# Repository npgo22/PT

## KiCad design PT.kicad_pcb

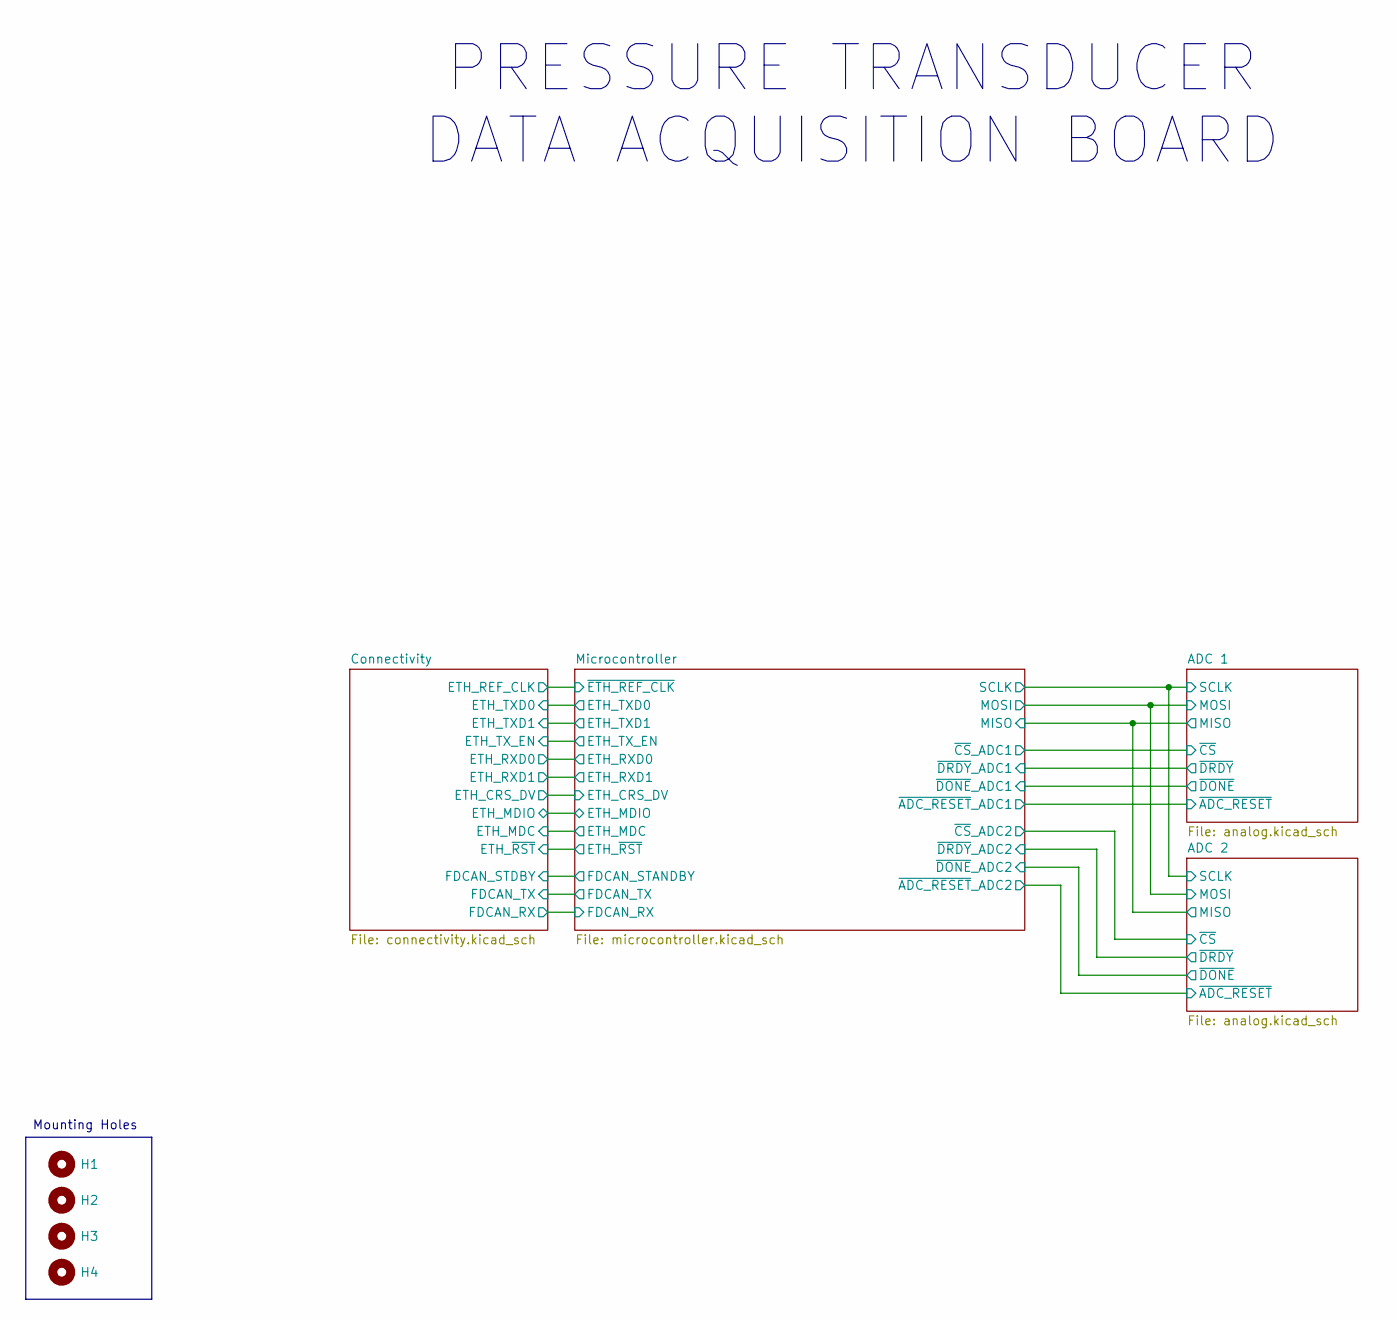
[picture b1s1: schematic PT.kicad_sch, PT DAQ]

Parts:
H1, H2, H3, H4: MountingHole; MountingHole_3.2mm_M3

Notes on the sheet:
PRESSURE TRANSDUCER DATA ACQUISITION BOARD
Mounting Holes

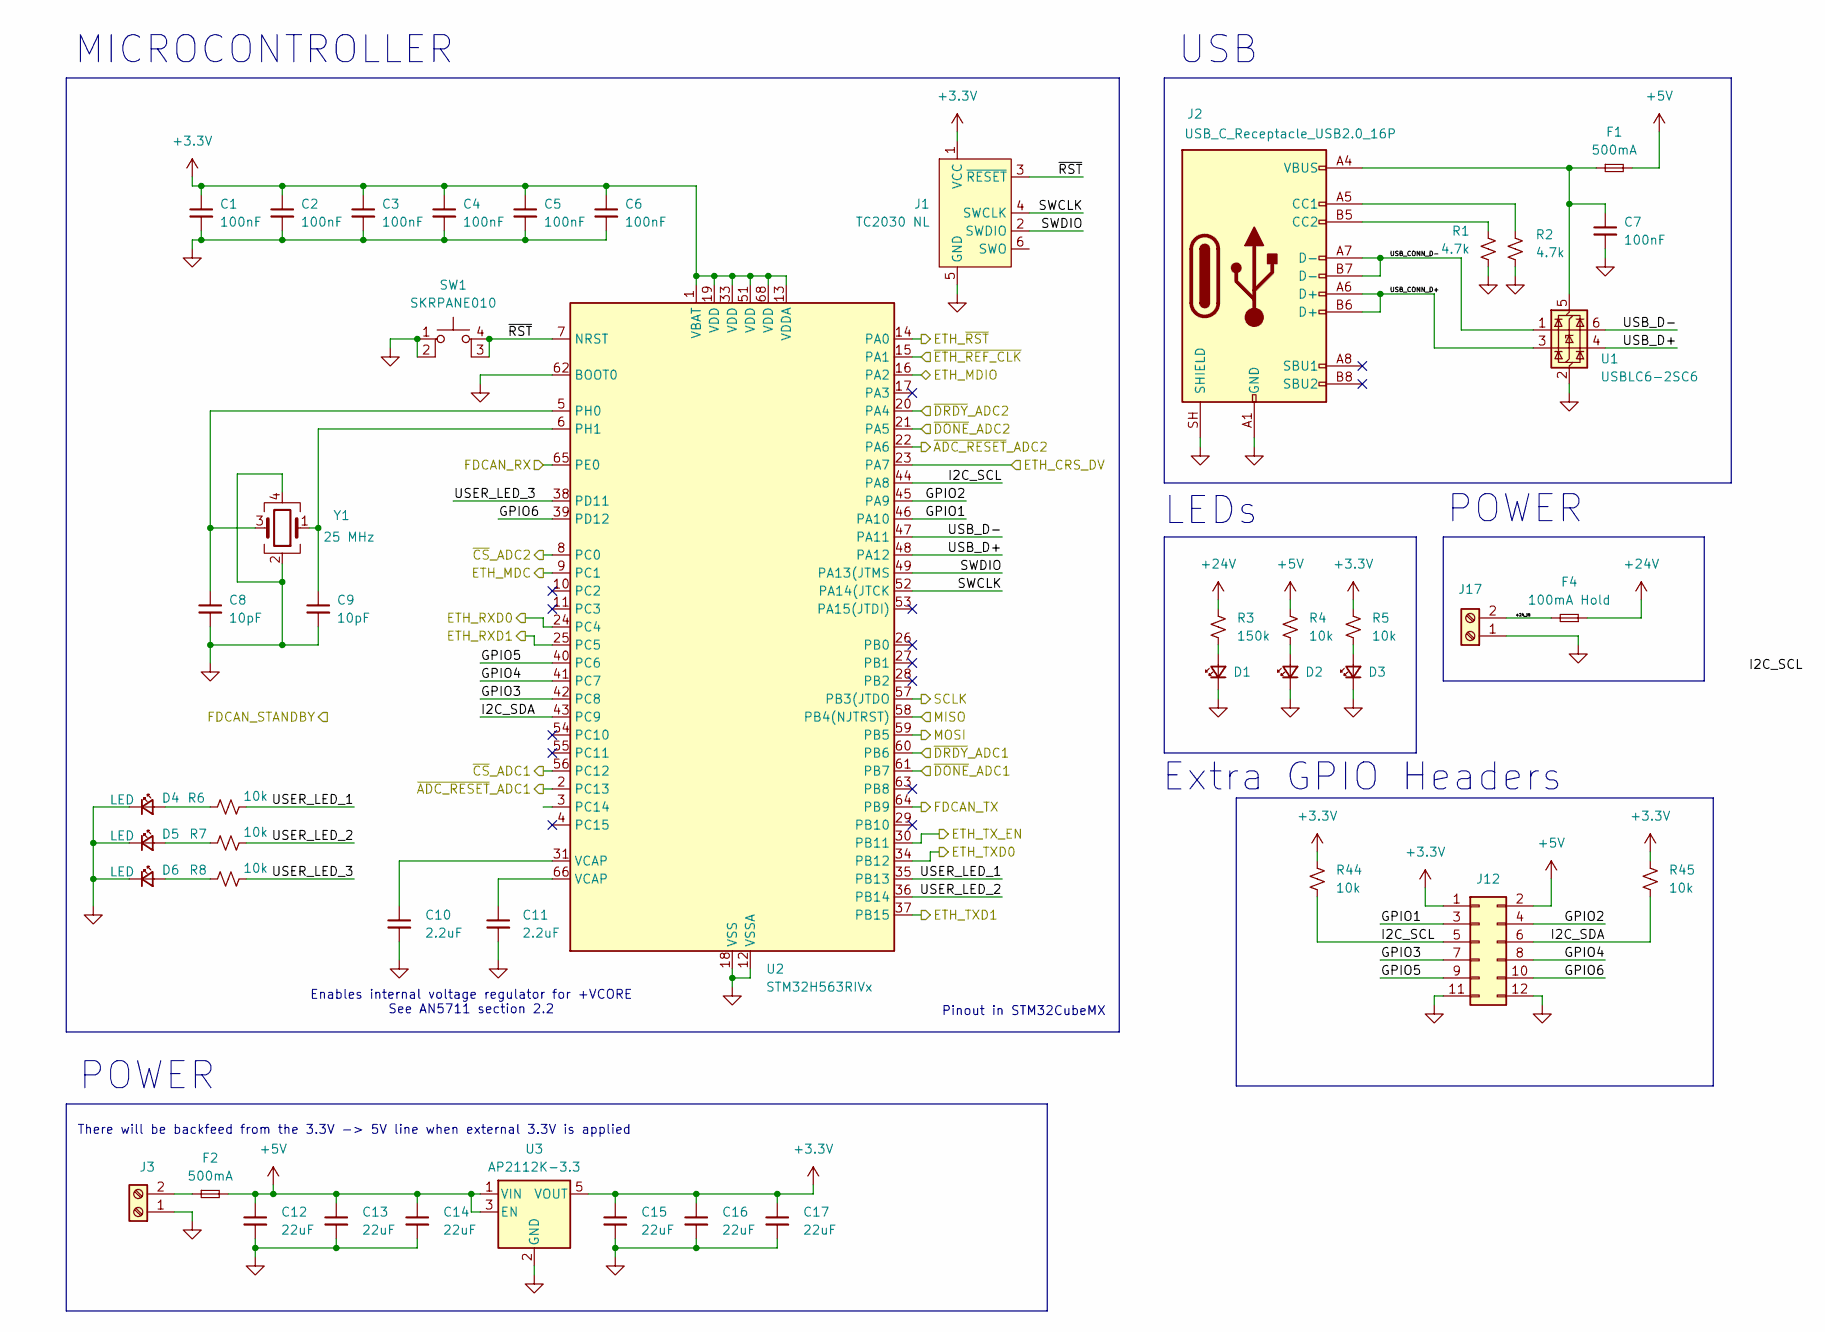
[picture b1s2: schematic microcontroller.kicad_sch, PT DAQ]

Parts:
C1, C2, C3, C4, C5, C6: 100nF; C_0603; LCSC C32949
C7: 100nF; C_0603
C8, C9: 10pF; C_0603; LCSC C32949
C10, C11: 2.2uF; C_0603; LCSC C170151
C12, C13, C14, C15, C16, C17: 22uF; C_0805; LCSC C602037
D1, D2, D3: LED; LED_0603
D4, D5, D6: LED; LED_0603; LCSC C965793
F1, F2: 500mA; Fuse_0805_2012Metric
F4: 100mA Hold; Fuse_0805_2012Metric
J1: TC2030 NL; Tag-Connect_TC2030-IDC-NL_2x03_P1.27mm_Vertical
J2: USB_C_Receptacle_USB2.0_16P; USB_C_Receptacle_HRO_TYPE-C-31-M-12
J3: Screw_Terminal_01x02; TerminalBlock_Phoenix_MPT-0,5-2-2.54_1x02_P2.54mm_Horizontal; LCSC C3029316
J12: Conn_02x06_Top_Bottom; IDC-Header_2x06_P2.54mm_Vertical
J17: Screw_Terminal_01x02; TerminalBlock_Phoenix_MPT-0,5-2-2.54_1x02_P2.54mm_Horizontal
R1, R2: 4.7k; R_0603
R3: 150k; R_0603
R4, R5, R44, R45: 10k; R_0603
R6, R7, R8: 10k; R_0603; LCSC C105875
SW1: SKRPANE010
U1: USBLC6-2SC6; SOT-23-6
U2: STM32H563RIVx; QFN-68-1EP_8x8mm_P0.4mm_EP6.4x6.4mm
U3: AP2112K-3.3; SOT-23-5
Y1: 25 MHz; 3225-4P-L; LCSC C2901668

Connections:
+3.3V: C1.1, C2.1, C3.1, C4.1, C5.1, C6.1, C15.1, C16.1, C17.1, J1.1 (VCC), J12.1, R5.1, R44.1, R45.1, U2.1 (VBAT), U2.13 (VDDA), U2.19 (VDD), U2.33 (VDD), U2.51 (VDD), U2.68 (VDD), U3.5 (VOUT); also elsewhere on the board
+5V: C12.1, C13.1, C14.1, F1.2, F2.2, J12.2, R4.1, U3.1 (VIN), U3.3 (EN); also elsewhere on the board
+24V: F4.1, R3.1; also elsewhere on the board
/ADC 1/MISO: U2.58 (PB4(NJTRST)); also elsewhere on the board
/ADC 1/MOSI: U2.59 (PB5); also elsewhere on the board
/ADC 1/SCLK: U2.57 (PB3(JTDO); also elsewhere on the board
/ADC 1/~ADC_RESET: U2.2 (PC13); also elsewhere on the board
/ADC 1/~CS: U2.56 (PC12); also elsewhere on the board
/ADC 1/~DONE: U2.61 (PB7); also elsewhere on the board
/ADC 1/~DRDY: U2.60 (PB6); also elsewhere on the board
/ADC 2/~ADC_RESET: U2.22 (PA6); also elsewhere on the board
/ADC 2/~CS: U2.8 (PC0); also elsewhere on the board
/ADC 2/~DONE: U2.21 (PA5); also elsewhere on the board
/ADC 2/~DRDY: U2.20 (PA4); also elsewhere on the board
/Connectivity/ETH_CRS_DV: U2.23 (PA7); also elsewhere on the board
/Connectivity/ETH_MDC: U2.9 (PC1); also elsewhere on the board
/Connectivity/ETH_MDIO: U2.16 (PA2); also elsewhere on the board
/Connectivity/ETH_REF_CLK: U2.15 (PA1); also elsewhere on the board
/Connectivity/ETH_RXD0: U2.24 (PC4); also elsewhere on the board
/Connectivity/ETH_RXD1: U2.25 (PC5); also elsewhere on the board
/Connectivity/ETH_TXD0: U2.34 (PB12); also elsewhere on the board
/Connectivity/ETH_TXD1: U2.37 (PB15); also elsewhere on the board
/Connectivity/ETH_TX_EN: U2.30 (PB11); also elsewhere on the board
/Connectivity/ETH_~RST: U2.14 (PA0); also elsewhere on the board
/Connectivity/FDCAN_RX: U2.65 (PE0); also elsewhere on the board
/Connectivity/FDCAN_TX: U2.64 (PB9); also elsewhere on the board
/Microcontroller/+24_IN: F4.2, J17.2
/Microcontroller/GPIO1: J12.3, U2.46 (PA10)
/Microcontroller/GPIO2: J12.4, U2.45 (PA9)
/Microcontroller/GPIO3: J12.7, U2.42 (PC8)
/Microcontroller/GPIO4: J12.8, U2.41 (PC7)
/Microcontroller/GPIO5: J12.9, U2.40 (PC6)
/Microcontroller/GPIO6: J12.10, U2.39 (PD12)
/Microcontroller/I2C_SCL: J12.5, R44.2, U2.44 (PA8)
/Microcontroller/I2C_SDA: J12.6, R45.2, U2.43 (PC9)
/Microcontroller/SWCLK: J1.4 (SWCLK), U2.52 (PA14(JTCK)
/Microcontroller/SWDIO: J1.2 (SWDIO), U2.49 (PA13(JTMS)
/Microcontroller/USB_CONN_D+: J2.A6 (D+), J2.B6 (D+), U1.3 (I/O2)
/Microcontroller/USB_CONN_D-: J2.A7 (D-), J2.B7 (D-), U1.1 (I/O1)
/Microcontroller/USB_D+: U1.4 (I/O2), U2.48 (PA12)
/Microcontroller/USB_D-: U1.6 (I/O1), U2.47 (PA11)
/Microcontroller/USER_LED_1: R6.2, U2.35 (PB13)
/Microcontroller/USER_LED_2: R7.2, U2.36 (PB14)
/Microcontroller/USER_LED_3: R8.2, U2.38 (PD11)
/Microcontroller/~RST: J1.3 (~RESET), SW1.3 (K), SW1.4 (A), U2.7 (NRST)
GND: C1.2, C2.2, C3.2, C4.2, C5.2, C6.2, C7.2, C8.2, C9.2, C10.2, C11.2, C12.2, C13.2, C14.2, C15.2, C16.2, C17.2, D1.1 (K), D2.1 (K), D3.1 (K), D4.1 (K), D5.1 (K), D6.1 (K), J1.5 (GND), J2.A1 (GND), J2.A12 (GND), J2.B1 (GND), J2.B12 (GND), J2.SH (SHIELD), J3.1, J12.11, J12.12, J17.1, R1.1, R2.2, SW1.1, SW1.2, U1.2 (GND), U2.12 (VSSA), U2.18 (VSS), U2.32 (VSS), U2.50 (VSS), U2.62 (BOOT0), U2.67 (VSS), U2.69 (VSS), U3.2 (GND), Y1.2, Y1.4; also elsewhere on the board
unnamed: C10.1, U2.31 (VCAP)
unnamed: C11.1, U2.66 (VCAP)
unnamed: D1.2 (A), R3.2
unnamed: D2.2 (A), R4.2
unnamed: D3.2 (A), R5.2
unnamed: D4.2 (A), R6.1
unnamed: D5.2 (A), R7.1
unnamed: D6.2 (A), R8.1
unnamed: J2.A5 (CC1), R2.1
unnamed: J2.B5 (CC2), R1.2
unnamed: F2.1, J3.2
unnamed: C7.1, F1.1, J2.A4 (VBUS), J2.A9 (VBUS), J2.B4 (VBUS), J2.B9 (VBUS), U1.5 (VBUS)
unnamed: C8.1, U2.5 (PH0), Y1.3
unnamed: C9.1, U2.6 (PH1), Y1.1

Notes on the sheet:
Enables internal voltage regulator for +VCORE See AN5711 section 2.2
MICROCONTROLLER
There will be backfeed from the 3.3V -> 5V line when external 3.3V is applied
Extra GPIO Headers
USB
POWER
Pinout in STM32CubeMX
LEDs

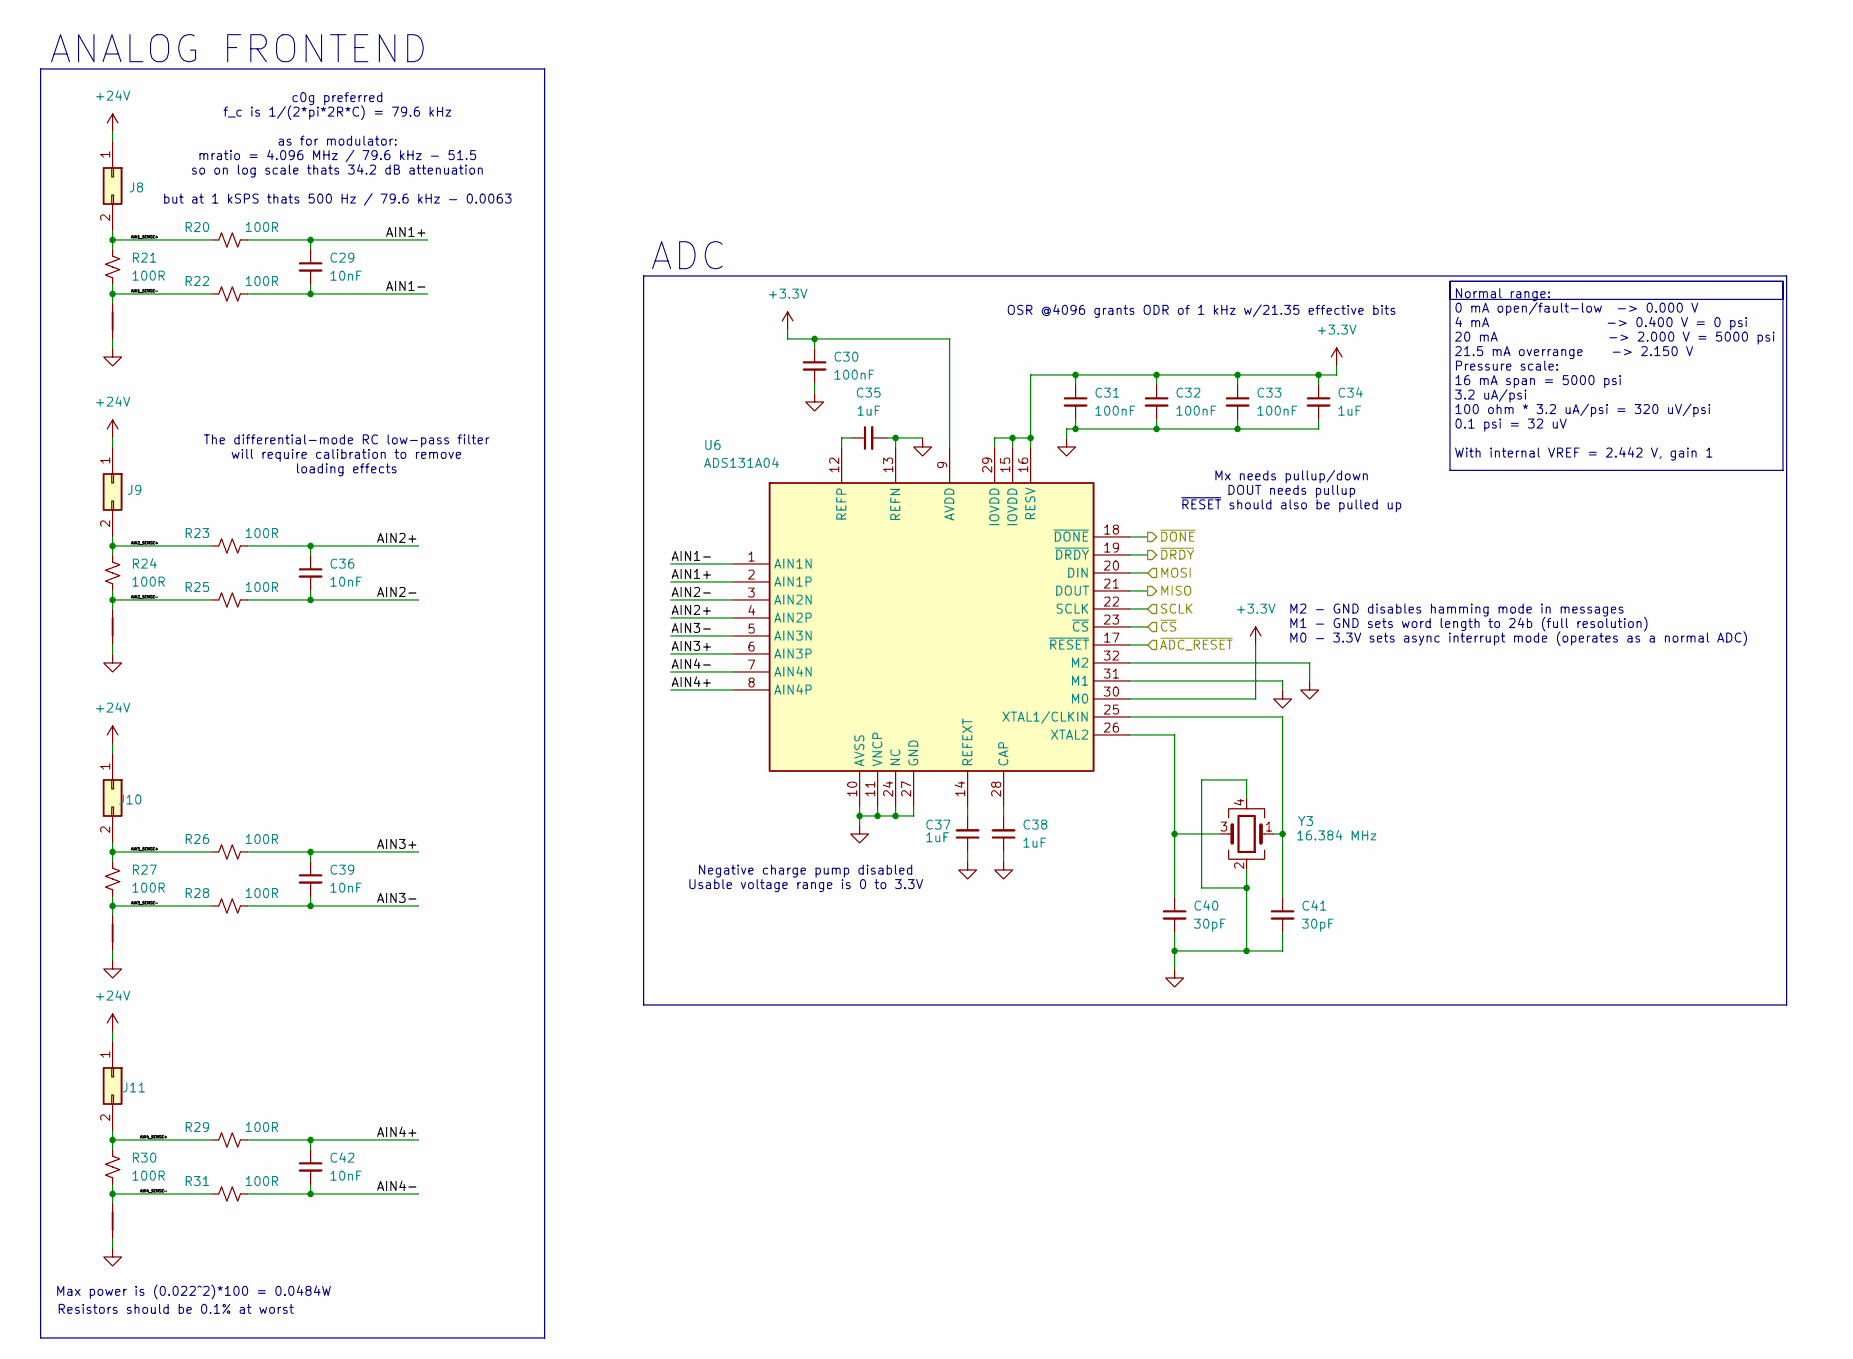
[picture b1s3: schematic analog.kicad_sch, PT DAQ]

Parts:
C29, C36, C39, C42: 10nF; C_0603
C30, C31, C32, C33: 100nF; C_0603
C34, C35, C37, C38: 1uF; C_0603
C40, C41: 30pF; C_0603; LCSC C32949
J8, J9, J10, J11: Conn_02x01; TerminalBlock_Phoenix_MPT-0,5-2-2.54_1x02_P2.54mm_Horizontal
NT1, NT2, NT3, NT4: NetTie_2; NetTie-2_SMD_Pad0.5mm
R20, R22, R23, R25, R26, R28, R29, R31: 100R; R_0603
R21, R24, R27, R30: 100R; R_0805
U6: ADS131A04; QFP-32_5x5_Pitch0.5mm
Y3: 16.384 MHz; 3225-4P-L; LCSC C2901668

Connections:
+3.3V: C30.1, C31.1, C32.1, C33.1, C34.1, U6.9 (AVDD), U6.15 (IOVDD), U6.16 (RESV), U6.29 (IOVDD), U6.30 (M0); also elsewhere on the board
+24V: J8.1, J9.1, J10.1, J11.1; also elsewhere on the board
/ADC 1/AIN1+: C29.1, R20.2, U6.2 (AIN1P)
/ADC 1/AIN1-: C29.2, R22.2, U6.1 (AIN1N)
/ADC 1/AIN1_SENSE+: J8.2, R20.1, R21.1
/ADC 1/AIN1_SENSE-: NT1.2, R21.2, R22.1
/ADC 1/AIN2+: C36.1, R23.2, U6.4 (AIN2P)
/ADC 1/AIN2-: C36.2, R25.2, U6.3 (AIN2N)
/ADC 1/AIN2_SENSE+: J9.2, R23.1, R24.1
/ADC 1/AIN2_SENSE-: NT2.2, R24.2, R25.1
/ADC 1/AIN3+: C39.1, R26.2, U6.6 (AIN3P)
/ADC 1/AIN3-: C39.2, R28.2, U6.5 (AIN3N)
/ADC 1/AIN3_SENSE+: J10.2, R26.1, R27.1
/ADC 1/AIN3_SENSE-: NT3.2, R27.2, R28.1
/ADC 1/AIN4+: C42.1, R29.2, U6.8 (AIN4P)
/ADC 1/AIN4-: C42.2, R31.2, U6.7 (AIN4N)
/ADC 1/AIN4_SENSE+: J11.2, R29.1, R30.1
/ADC 1/AIN4_SENSE-: NT4.2, R30.2, R31.1
/ADC 1/MISO: U6.21 (DOUT); also elsewhere on the board
/ADC 1/MOSI: U6.20 (DIN); also elsewhere on the board
/ADC 1/SCLK: U6.22 (SCLK); also elsewhere on the board
/ADC 1/~ADC_RESET: U6.17 (~RESET); also elsewhere on the board
/ADC 1/~CS: U6.23 (~CS); also elsewhere on the board
/ADC 1/~DONE: U6.18 (~DONE); also elsewhere on the board
/ADC 1/~DRDY: U6.19 (~DRDY); also elsewhere on the board
GND: C30.2, C31.2, C32.2, C33.2, C34.2, C35.2, C37.1, C38.1, C40.2, C41.2, NT1.1, NT2.1, NT3.1, NT4.1, U6.10 (AVSS), U6.11 (VNCP), U6.13 (REFN), U6.24 (NC), U6.27 (GND), U6.31 (M1), U6.32 (M2), Y3.2, Y3.4; also elsewhere on the board
unnamed: C38.2, U6.28 (CAP)
unnamed: C37.2, U6.14 (REFEXT)
unnamed: C35.1, U6.12 (REFP)
unnamed: C41.1, U6.25 (XTAL1/CLKIN), Y3.1
unnamed: C40.1, U6.26 (XTAL2), Y3.3

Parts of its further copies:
C43, C50, C53, C56: 10nF; C_0603
C44, C45, C46, C47: 100nF; C_0603
C48, C49, C51, C52: 1uF; C_0603
C54, C55: 30pF; C_0603; LCSC C32949
J13, J14, J15, J16: Conn_02x01; TerminalBlock_Phoenix_MPT-0,5-2-2.54_1x02_P2.54mm_Horizontal
NT5, NT6, NT7, NT8: NetTie_2; NetTie-2_SMD_Pad0.5mm
R32, R34, R35, R37, R38, R40, R41, R43: 100R; R_0603
R33, R36, R39, R42: 100R; R_0805
U7: ADS131A04; QFP-32_5x5_Pitch0.5mm
Y4: 16.384 MHz; 3225-4P-L; LCSC C2901668

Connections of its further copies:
+3.3V: C44.1, C45.1, C46.1, C47.1, C48.1, U7.9 (AVDD), U7.15 (IOVDD), U7.16 (RESV), U7.29 (IOVDD), U7.30 (M0); also elsewhere on the board
+24V: J13.1, J14.1, J15.1, J16.1; also elsewhere on the board
/ADC 1/MISO: U7.21 (DOUT); also elsewhere on the board
/ADC 1/MOSI: U7.20 (DIN); also elsewhere on the board
/ADC 1/SCLK: U7.22 (SCLK); also elsewhere on the board
/ADC 2/AIN1+: C43.1, R32.2, U7.2 (AIN1P)
/ADC 2/AIN1-: C43.2, R34.2, U7.1 (AIN1N)
/ADC 2/AIN1_SENSE+: J13.2, R32.1, R33.1
/ADC 2/AIN1_SENSE-: NT5.2, R33.2, R34.1
/ADC 2/AIN2+: C50.1, R35.2, U7.4 (AIN2P)
/ADC 2/AIN2-: C50.2, R37.2, U7.3 (AIN2N)
/ADC 2/AIN2_SENSE+: J14.2, R35.1, R36.1
/ADC 2/AIN2_SENSE-: NT6.2, R36.2, R37.1
/ADC 2/AIN3+: C53.1, R38.2, U7.6 (AIN3P)
/ADC 2/AIN3-: C53.2, R40.2, U7.5 (AIN3N)
/ADC 2/AIN3_SENSE+: J15.2, R38.1, R39.1
/ADC 2/AIN3_SENSE-: NT7.2, R39.2, R40.1
/ADC 2/AIN4+: C56.1, R41.2, U7.8 (AIN4P)
/ADC 2/AIN4-: C56.2, R43.2, U7.7 (AIN4N)
/ADC 2/AIN4_SENSE+: J16.2, R41.1, R42.1
/ADC 2/AIN4_SENSE-: NT8.2, R42.2, R43.1
/ADC 2/~ADC_RESET: U7.17 (~RESET); also elsewhere on the board
/ADC 2/~CS: U7.23 (~CS); also elsewhere on the board
/ADC 2/~DONE: U7.18 (~DONE); also elsewhere on the board
/ADC 2/~DRDY: U7.19 (~DRDY); also elsewhere on the board
GND: C44.2, C45.2, C46.2, C47.2, C48.2, C49.2, C51.1, C52.1, C54.2, C55.2, NT5.1, NT6.1, NT7.1, NT8.1, U7.10 (AVSS), U7.11 (VNCP), U7.13 (REFN), U7.24 (NC), U7.27 (GND), U7.31 (M1), U7.32 (M2), Y4.2, Y4.4; also elsewhere on the board
unnamed: C52.2, U7.28 (CAP)
unnamed: C51.2, U7.14 (REFEXT)
unnamed: C49.1, U7.12 (REFP)
unnamed: C55.1, U7.25 (XTAL1/CLKIN), Y4.1
unnamed: C54.1, U7.26 (XTAL2), Y4.3

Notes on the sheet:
M2 - GND disables hamming mode in messages M1 - GND sets word length to 24b (full resolution) M0 - 3.3V sets async interrupt mode (operates as a normal ADC)
c0g preferred f_c is 1/(2*pi*2R*C) = 79.6 kHz as for modulator: mratio = 4.096 MHz / 79.6 kHz - 51.5 so on log scale thats 34.2 dB attenuation but at 1 kSPS thats 500 Hz / 79.6 kHz - 0.0063
Negative charge pump disabled Usable voltage range is 0 to 3.3V
Resistors should be 0.1% at worst
Max power is (0.022^2)*100 = 0.0484W
Normal range: 0 mA open/fault-low -> 0.000 V 4 mA -> 0.400 V = 0 psi 20 mA -> 2.000 V = 5000 psi 21.5 mA overrange -> 2.150 V Pressure scale: 16 mA span = 5000 psi 3.2 uA/psi 100 ohm * 3.2 uA/psi = 320 uV/psi 0.1 psi = 32 uV With internal VREF = 2.442 V, gain 1
ANALOG FRONTEND
OSR @4096 grants ODR of 1 kHz w/21.35 effective bits
Mx needs pullup/down DOUT needs pullup ~{RESET} should also be pulled up
ADC
The differential-mode RC low-pass filter will require calibration to remove loading effects

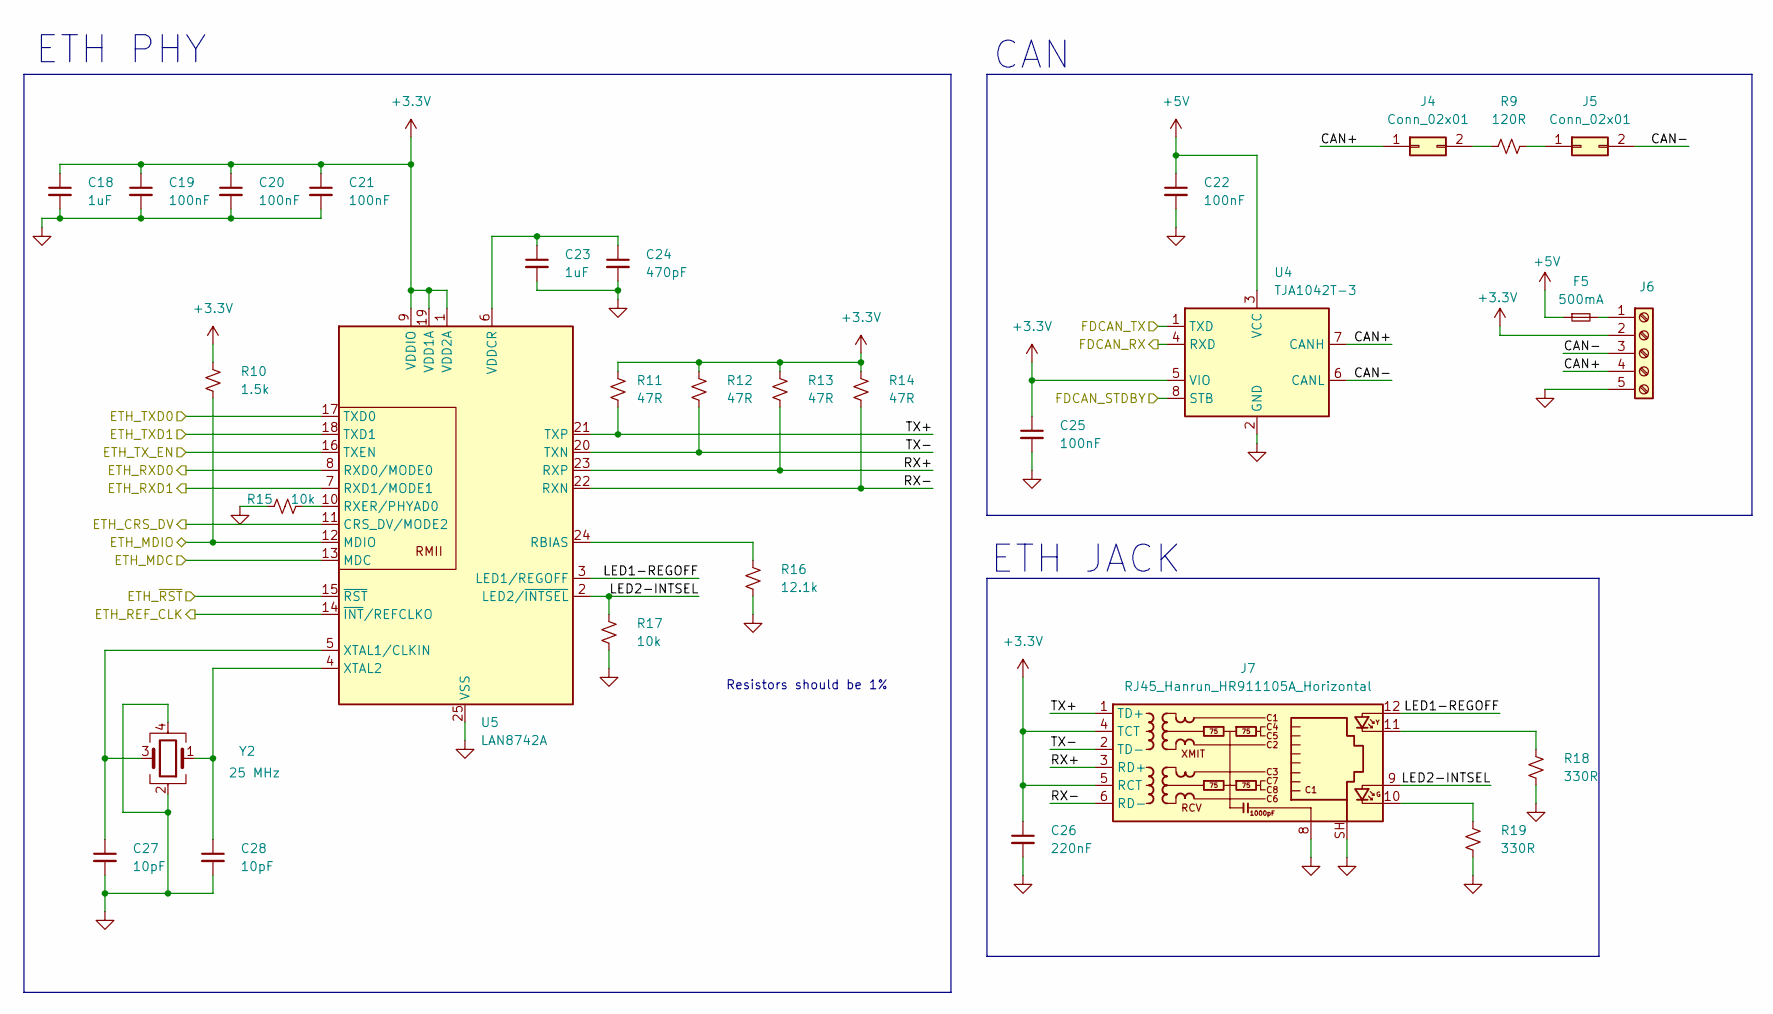
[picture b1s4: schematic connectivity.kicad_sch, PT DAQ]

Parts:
C18, C23: 1uF; C_0603; LCSC C602037
C19, C20, C21, C22, C25: 100nF; C_0603; LCSC C1525
C24: 470pF; C_0603; LCSC C602037
C26: 220nF; C_0603; LCSC C1525
C27, C28: 10pF; C_0603; LCSC C32949
F5: 500mA; Fuse_0805_2012Metric
J4, J5: Conn_02x01; PinHeader_2x01_P2.54mm_Vertical
J6: Screw_Terminal_01x05; TerminalBlock_Phoenix_MPT-0,5-5-2.54_1x05_P2.54mm_Horizontal
J7: RJ45_Hanrun_HR911105A_Horizontal; LCSC C12074
R9: 120R; R_0603
R10: 1.5k; R_0603; LCSC C60490
R11, R12, R13, R14: 47R; R_0603; LCSC C87044
R15: 10k; R_0603
R16: 12.1k; R_0603; LCSC C25852
R17: 10k; R_0603; LCSC C60490
R18, R19: 330R; R_0603; LCSC C105875
U4: TJA1042T-3; SOIC-8_3.9x4.9mm_P1.27mm; LCSC C22445414
U5: LAN8742A; VQFN-24-1EP_4x4mm_P0.5mm_EP2.5x2.5mm_ThermalVias
Y2: 25 MHz; 3225-4P-L; LCSC C2901668

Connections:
+3.3V: C18.1, C19.1, C20.1, C21.1, C25.1, C26.1, J6.2, J7.4 (TCT), J7.5 (RCT), R10.1, R11.1, R12.1, R13.1, R14.1, U4.5 (VIO), U5.1 (VDD2A), U5.9 (VDDIO), U5.19 (VDD1A); also elsewhere on the board
+5V: C22.1, F5.1, U4.3 (VCC); also elsewhere on the board
/Connectivity/CAN+: J4.1, J6.4, U4.7 (CANH)
/Connectivity/CAN-: J5.2, J6.3, U4.6 (CANL)
/Connectivity/ETH_CRS_DV: U5.11 (CRS_DV/MODE2); also elsewhere on the board
/Connectivity/ETH_MDC: U5.13 (MDC); also elsewhere on the board
/Connectivity/ETH_MDIO: R10.2, U5.12 (MDIO); also elsewhere on the board
/Connectivity/ETH_REF_CLK: U5.14 (~INT/REFCLKO); also elsewhere on the board
/Connectivity/ETH_RXD0: U5.8 (RXD0/MODE0); also elsewhere on the board
/Connectivity/ETH_RXD1: U5.7 (RXD1/MODE1); also elsewhere on the board
/Connectivity/ETH_TXD0: U5.17 (TXD0); also elsewhere on the board
/Connectivity/ETH_TXD1: U5.18 (TXD1); also elsewhere on the board
/Connectivity/ETH_TX_EN: U5.16 (TXEN); also elsewhere on the board
/Connectivity/ETH_~RST: U5.15 (~RST); also elsewhere on the board
/Connectivity/FDCAN_RX: U4.4 (RXD); also elsewhere on the board
/Connectivity/FDCAN_STDBY: U4.8 (STB)
/Connectivity/FDCAN_TX: U4.1 (TXD); also elsewhere on the board
/Connectivity/LED1-REGOFF: J7.12, U5.3 (LED1/REGOFF)
/Connectivity/LED2-INTSEL: J7.9, R17.1, U5.2 (LED2/~INTSEL)
/Connectivity/RX+: J7.3 (RD+), R13.2, U5.23 (RXP)
/Connectivity/RX-: J7.6 (RD-), R14.2, U5.22 (RXN)
/Connectivity/TX+: J7.1 (TD+), R11.2, U5.21 (TXP)
/Connectivity/TX-: J7.2 (TD-), R12.2, U5.20 (TXN)
GND: C18.2, C19.2, C20.2, C21.2, C22.2, C23.2, C24.2, C25.2, C26.2, C27.2, C28.2, J6.5, J7.8, J7.SH, R15.1, R16.2, R17.2, R18.2, R19.2, U4.2 (GND), U5.25 (VSS), Y2.2, Y2.4; also elsewhere on the board
unnamed: J4.2, R9.1
unnamed: J5.1, R9.2
unnamed: F5.2, J6.1
unnamed: J7.10, R19.1
unnamed: J7.11, R18.1
unnamed: R16.1, U5.24 (RBIAS)
unnamed: R15.2, U5.10 (RXER/PHYAD0)
unnamed: C23.1, C24.1, U5.6 (VDDCR)
unnamed: C27.1, U5.5 (XTAL1/CLKIN), Y2.3
unnamed: C28.1, U5.4 (XTAL2), Y2.1

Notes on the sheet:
ETH PHY
CAN
Resistors should be 1%
ETH JACK

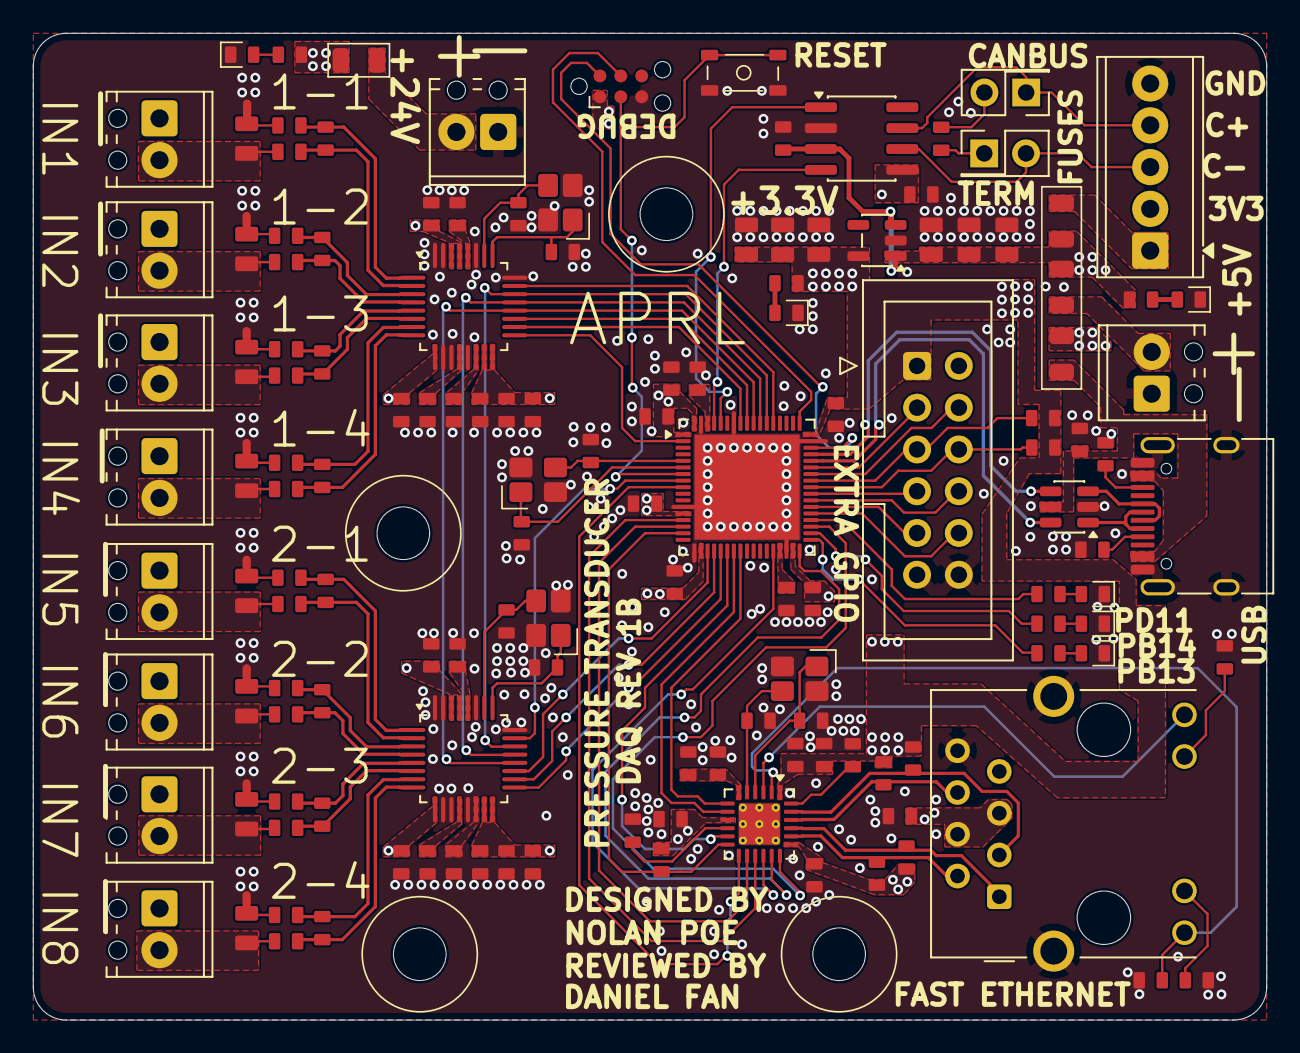
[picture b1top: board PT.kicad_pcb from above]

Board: 4 copper layers, 75.0 x 60.0 mm, 152 parts (0 on the bottom side), 120 nets.

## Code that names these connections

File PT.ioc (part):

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Mcu.Name=STM32H563RIVx
Mcu.Package=VFQFPN68
Mcu.UserName=STM32H563RIVx
PA0.GPIOParameters=GPIO_Label
PA0.GPIO_Label=ETH_nRST
PA0.Signal=GPIO_Output
PA1.Mode=RMII
PA1.Signal=ETH_REF_CLK
PA10.GPIOParameters=GPIO_Label
PA10.GPIO_Label=USER_LED_3
PA10.Signal=GPIO_Output
PA11.Mode=Device
PA11.Signal=USB_DM
PA12.Mode=Device
PA12.Signal=USB_DP
PA13(JTMS/SWDIO).Mode=Serial_Wire
PA13(JTMS/SWDIO).Signal=DEBUG_JTMS-SWDIO
PA14(JTCK/SWCLK).Mode=Serial_Wire
PA14(JTCK/SWCLK).Signal=DEBUG_JTCK-SWCLK
PA15(JTDI).GPIOParameters=GPIO_Label
PA15(JTDI).GPIO_Label=M0
PA15(JTDI).Signal=GPIO_Output
PA2.Mode=RMII
PA2.Signal=ETH_MDIO
PA5.Mode=RMII
PA5.Signal=ETH_TX_EN
PA7.Mode=RMII
PA7.Signal=ETH_CRS_DV
PA8.GPIOParameters=GPIO_Label
PA8.GPIO_Label=USER_LED_1
PA8.Signal=GPIO_Output
PA9.GPIOParameters=GPIO_Label
PA9.GPIO_Label=USER_LED_2
PA9.Signal=GPIO_Output
PB12.Mode=RMII
PB12.Signal=ETH_TXD0
PB15.Mode=RMII
PB15.Signal=ETH_TXD1
PB3(JTDO/TRACESWO).Mode=Full_Duplex_Master
PB3(JTDO/TRACESWO).Signal=SPI1_SCK
PB4(NJTRST).Mode=Full_Duplex_Master
PB4(NJTRST).Signal=SPI1_MISO
PB5.Mode=Full_Duplex_Master
PB5.Signal=SPI1_MOSI
PB6.GPIOParameters=GPIO_Label
PB6.GPIO_Label=nDRDY
PB6.Signal=GPIO_Input
PB7.GPIOParameters=GPIO_Label
PB7.GPIO_Label=nCS
PB7.Signal=GPIO_Output
PB9.Mode=FDCAN_Activate
PB9.Signal=FDCAN1_TX
PC1.Mode=RMII
PC1.Signal=ETH_MDC
PC10.GPIOParameters=GPIO_Label
PC10.GPIO_Label=M2
PC10.Signal=GPIO_Output
PC11.GPIOParameters=GPIO_Label
PC11.GPIO_Label=M1
PC11.Signal=GPIO_Output
PC12.GPIOParameters=GPIO_Label
PC12.GPIO_Label=nDONE
PC12.Signal=GPIO_Output
PC13.GPIOParameters=GPIO_Label
PC13.GPIO_Label=FDCAN_STDBY
PC13.Signal=GPIO_Output
PC14-OSC32_IN(OSC32_IN).GPIOParameters=GPIO_Label
PC14-OSC32_IN(OSC32_IN).GPIO_Label=ADC_RESET
PC14-OSC32_IN(OSC32_IN).Signal=GPIO_Output
PC4.Mode=RMII
PC4.Signal=ETH_RXD0
PC5.Mode=RMII
PC5.Signal=ETH_RXD1
PD12.GPIOParameters=GPIO_Label
PD12.GPIO_Label=ETH_RXER
PD12.Signal=GPIO_Output
PE0.Mode=FDCAN_Activate
PE0.Signal=FDCAN1_RX
PH0-OSC_IN(PH0).Mode=HSE-External-Oscillator
PH0-OSC_IN(PH0).Signal=RCC_OSC_IN
PH1-OSC_OUT(PH1).Mode=HSE-External-Oscillator
PH1-OSC_OUT(PH1).Signal=RCC_OSC_OUT
RCC.HSE_VALUE=25000000
RCC.SYSCLKFreq_VALUE=32000000
board=custom

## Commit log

2026-01-01 Disable ERC/DRC in CI
2026-01-01 Fix kibot filename
2026-01-01 Disable scaling on prints
2026-01-01 Device is a sink not a source
2026-01-02 Fix fill problems
2026-01-02 Fix ethernet routing
2026-01-02 small via spacing
2026-01-02 Add extra indicator for CAN
2026-01-11 Change fuse footprints
2026-01-11 Update fuse footprint, fix ERC
2026-01-11 Remove fuse reference designators
2026-01-11 Update kibot config
2026-01-13 Initial release A1
2026-05-16 Pranked by propfeed and engine again
2026-05-16 Fix the regulator label
2026-05-17 Swap TPS7A20 for LP5907 (Daniel yelled at me again)
2026-05-17 Remove accidental Fuse silkscreen reference designators
2026-05-19 Swap to STM32H563RIV6, and add split +3.3V and +3.3VA
2026-05-20 June 20th is not real and cant hurt me
2026-05-20 Timeline is not real
2026-05-22 Remove LP5907
2026-05-22 Use sheet pins instead of global labels where appropriate
2026-05-22 Use static configurations for ADC instead of using MCU for pullups/downs
2026-05-23 holy hell 2 adcs
2026-05-24 New layout just dropped (need to change silkscreen on USB and update PT.ioc)
2026-06-29 Add renovate.json
